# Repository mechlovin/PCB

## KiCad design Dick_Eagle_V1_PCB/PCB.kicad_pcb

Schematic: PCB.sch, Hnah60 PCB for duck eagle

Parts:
C1: 106; CP_Tantalum_3216
C2, C3: 105; C_0805_2012Metric
C4, C5, C6, C7: 104; C_0805_2012Metric
D1, D2, D3, D4, D5, D6, D7, D8, D9, D10, D11, D12, D13, D14, D15, D16, D17, D18, D19, D20, D21, D22, D23, D24, D25, D26, D27, D28, D29, D30, D31, D32, D33, D34, D35, D36, D37, D38, D39, D40, D41, D42, D43, D44, D45, D46, D47, D48, D49, D50, D51, D52, D53, D54, D56, D57, D58, D59, D60, D62, D63, D64, D65, D66: 4148; D_0805_Mab_ideal
D61, D67, D68, D69, D70, D71, D72, D73, D74, D75, D76, D77, D78, D79, D80, D81, D82, D83, D84, D85, D86, D87, D88, D89, D90, D92, D93, D94, D95, D97, D98, D99, D100, D101, D102, D103, D104, D105, D107, D108, D109, D110, D111, D112, D113, D114, D115, D116, D117, D118, D119, D120, D121, D122, D123, D124, D125, D126, D127, D128, D129, D130, D131, D132, D133, D134, D135, D136, D137, D138, D139, D153, D154, D155, D156, D157, D158: SMD; CHERRY_MX_LED_3MM
D91, D96, D106, D140: SK6812MINI; LED_SK6812MINI_PLCC4_3.5x3.5mm_P1.75mm
H1, H18, H22: Screw; Screw_M2_Hole
H2, H4, H6, H8, H11, H13, H14, H15, H16, H17, H19, H24: Stablilizer; Cherry_Stab_PCBMounted
H3, H5, H7, H9, H10, H12, H20, H21, H23: Screw; Screw_M2_hole_long_oval
J1: AVR-ISP-6; AVR_ISP_6
J2: Conn_01x06_Female; PinHeader_1x06_P1.27mm_Vertical
J3: USB_B_Mini; USB_MINIB
Q1: FDS9926A; SOIC-8_3.9x4.9mm_P1.27mm
R1, R2: 5k1; R_0805_2012Metric
R3, R6: 10k; R_0805_2012Metric
R4, R5: 22R; R_0805_2012Metric
R7, R8, R9, R10, R11, R12, R13, R14, R15, R16, R17, R18, R19, R20, R21, R22, R23, R24, R25, R27, R28, R29, R30, R32, R33, R34, R35, R37, R38, R39, R40, R41, R42, R43, R44, R45, R47, R48, R49, R50, R52, R53, R54, R55, R56, R57, R58, R59, R60, R61, R62, R63, R64, R65, R66, R67, R68, R69, R70, R71, R72, R73, R74, R75, R76: 330; R_0805_2012Metric
R26: 3300; R_0805_2012Metric
SW1: ESC; CHERRY_PCB_100H
SW2: TAB; CHERRY_PCB_100H
SW3, SW4: CAPS; CHERRY_PCB_100H
SW5, SW69, SW75: SHIFT; CHERRY_PCB_100H
SW6, SW7: CONTROL; CHERRY_PCB_100H
SW8: 1; CHERRY_PCB_100H
SW9: Q; CHERRY_PCB_100H
SW10: A; CHERRY_PCB_100H
SW11: Z; CHERRY_PCB_100H
SW12, SW44, SW49, SW61: GUI; CHERRY_PCB_100H
SW13: 2; CHERRY_PCB_100H
SW14: W; CHERRY_PCB_100H
SW15: S; CHERRY_PCB_100H
SW16: X; CHERRY_PCB_100H
SW17, SW43, SW50: ALTERNATE; CHERRY_PCB_100H
SW18: 3; CHERRY_PCB_100H
SW19: E; CHERRY_PCB_100H
SW20: D; CHERRY_PCB_100H
SW21: C; CHERRY_PCB_100H
SW22: 4; CHERRY_PCB_100H
SW23: R; CHERRY_PCB_100H
SW24: F; CHERRY_PCB_100H
SW25: V; CHERRY_PCB_100H
SW26: 5; CHERRY_PCB_100H
SW27: T; CHERRY_PCB_100H
SW28: G; CHERRY_PCB_100H
SW29: B; CHERRY_PCB_100H
SW30: 6; CHERRY_PCB_100H
SW31: Y; CHERRY_PCB_100H
SW32: H; CHERRY_PCB_100H
SW33: N; CHERRY_PCB_100H
SW34, SW59: SPACE; CHERRY_PCB_100H
SW35: 7; CHERRY_PCB_100H
SW36: U; CHERRY_PCB_100H
SW37: J; CHERRY_PCB_100H
SW38: M; CHERRY_PCB_100H
SW39: 8; CHERRY_PCB_100H
SW40: I; CHERRY_PCB_100H
SW41: K; CHERRY_PCB_100H
SW42: COMMA; CHERRY_PCB_100H
SW45: 9; CHERRY_PCB_100H
SW46: O; CHERRY_PCB_100H
SW47: L; CHERRY_PCB_100H
SW48: DOT; CHERRY_PCB_100H
SW51: 0; CHERRY_PCB_100H
SW52: P; CHERRY_PCB_100H
SW53: SCOLON; CHERRY_PCB_100H
SW54: SLASH; CHERRY_PCB_100H
SW55, SW66: APP; CHERRY_PCB_100H
SW56: MINUS; CHERRY_PCB_100H
SW57: LBRC; CHERRY_PCB_100H
SW58: QUOTE; CHERRY_PCB_100H
SW62, SW68: CTRL; CHERRY_PCB_100H
SW63: EQUAL; CHERRY_PCB_100H
SW64: RBRC; CHERRY_PCB_100H
SW65: HASH; CHERRY_PCB_100H
SW67: UP; CHERRY_PCB_100H
SW70, SW71: BSPC; CHERRY_PCB_100H
SW72: BSLS; CHERRY_PCB_100H
SW73, SW74: ENTER; CHERRY_PCB_100H
SW76: AFTER BSPC; CHERRY_PCB_100H
SW77: Reset; SW_SPST_FSMSM
U1: ATMEGA32U4; TQFP-44_Pitch0.8mm
USB1: HRO-TYPE-C-31-M-12; USB_MINI_MAB
Y1: 16MHz; Resonator_SMD_muRata_CSTxExxV-3Pin_3.0x1.1mm

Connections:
/Backlight-layout1: Q1.2 (G1), Q1.4 (G2), U1.12 ((PCINT7/OC0A/OC1C/~RTS~)PB7)
/Col1-layout1: J1.4 (MOSI), SW1.2, SW2.2, SW3.2, SW4.1, SW5.2, SW6.2, SW7.2, U1.10 ((PDI/PCINT2/MOSI)PB2)
/Col2-layout1: J1.3 (SCK), SW8.2, SW9.2, SW10.2, SW11.2, SW12.2, SW44.2, U1.9 ((PCINT1/SCLK)PB1)
/Col3-layout1: J1.1 (MISO), SW13.2, SW14.2, SW15.2, SW16.2, SW17.2, SW50.2, U1.11 ((PDO/PCINT3/MISO)PB3)
/Col4-layout1: SW18.2, SW19.2, SW20.2, SW21.2, U1.36 ((ADC7/TDI)PF7)
/Col5-layout1: SW22.2, SW23.2, SW24.2, SW25.2, U1.37 ((ADC6/TDO)PF6)
/Col6-layout1: SW26.2, SW27.2, SW28.2, SW29.2, U1.38 ((ADC5/TMS)PF5)
/Col7-layout1: SW30.2, SW31.2, SW32.2, SW33.2, SW34.2, SW59.2, U1.41 ((ADC0)PF0)
/Col8-layout1: SW35.2, SW36.2, SW37.2, SW38.2, U1.39 ((ADC4/TCK)PF4)
/Col9-layout1: SW39.2, SW40.2, SW41.2, SW42.2, U1.40 ((ADC1)PF1)
/Col10-layout1: SW43.2, SW45.2, SW46.2, SW47.2, SW48.2, U1.22 ((XCK1/~CTS~)PD5)
/Col11-layout1: SW49.2, SW51.2, SW52.2, SW53.2, SW54.2, SW61.2, U1.25 ((ICP1/ADC8)PD4)
/Col12-layout1: SW55.2, SW56.2, SW57.2, SW58.2, SW66.2, U1.26 ((T1/~OC4D~/ADC9)PD6)
/Col13-layout1: SW62.2, SW63.2, SW64.2, SW65.2, SW68.2, SW69.2, SW75.2, U1.27 ((T0/OC4D/ADC10)PD7)
/Col14-layout1: SW67.2, SW70.2, SW71.2, SW72.2, SW73.1, SW74.2, SW76.2, U1.28 ((PCINT4/ADC11)PB4)
/RGB-layout1: R6.2, R26.1, U1.33 ((~HWB~)PE2)
/Reset: J1.5 (~RST), R3.1, SW77.2, U1.13 (~RESET~)
/caps_led: D69.2 (A), D137.1 (K), U1.8 ((SS/PCINT0)PB0)
/row1-layout1: D1.1 (K), D6.1 (K), D11.1 (K), D16.1 (K), D20.1 (K), D24.1 (K), D28.1 (K), D33.1 (K), D37.1 (K), D42.1 (K), D47.1 (K), D52.1 (K), D57.1 (K), D62.1 (K), U1.31 ((OC3A/~OC4A~)PC6)
/row2-layout1: D2.1 (K), D7.1 (K), D12.1 (K), D17.1 (K), D21.1 (K), D25.1 (K), D29.1 (K), D34.1 (K), D38.1 (K), D43.1 (K), D48.1 (K), D53.1 (K), D58.1 (K), D63.1 (K), U1.32 ((ICP3/CLK0/OC4A)PC7)
/row3-layout1: D3.1 (K), D8.1 (K), D13.1 (K), D18.1 (K), D22.1 (K), D26.1 (K), D30.1 (K), D35.1 (K), D39.1 (K), D44.1 (K), D49.1 (K), D54.1 (K), D59.1 (K), D64.1 (K), U1.1 ((INT6/AIN0)PE6)
/row4-layout1: D4.1 (K), D9.1 (K), D14.1 (K), D19.1 (K), D23.1 (K), D27.1 (K), D31.1 (K), D36.1 (K), D40.1 (K), D45.1 (K), D50.1 (K), D60.1 (K), D65.1 (K), U1.30 ((PCINT6/OC1B/OC4B/ADC13)PB6)
/row5-layout1: D5.1 (K), D10.1 (K), D15.1 (K), D32.1 (K), D41.1 (K), D46.1 (K), D51.1 (K), D56.1 (K), D66.1 (K), U1.29 ((PCINT5/OC1A/~OC4B~/ADC12)PB5)
GND: C1.2, C2.2, C3.2, C4.2, C5.2, C6.2, C7.2, D61.1 (K), D67.2 (A), D68.2 (A), D70.2 (A), D71.2 (A), D72.2 (A), D73.2 (A), D74.2 (A), D75.2 (A), D76.2 (A), D77.2 (A), D78.2 (A), D79.2 (A), D80.2 (A), D81.2 (A), D82.2 (A), D83.2 (A), D84.2 (A), D85.2 (A), D86.2 (A), D87.2 (A), D88.2 (A), D89.2 (A), D90.2 (A), D91.2 (VSS), D92.2 (A), D93.2 (A), D94.2 (A), D95.2 (A), D96.2 (VSS), D97.2 (A), D98.2 (A), D99.2 (A), D100.2 (A), D101.2 (A), D102.2 (A), D103.2 (A), D104.2 (A), D105.2 (A), D106.2 (VSS), D107.2 (A), D108.2 (A), D109.2 (A), D110.2 (A), D111.1 (K), D112.2 (A), D113.2 (A), D114.2 (A), D115.2 (A), D116.2 (A), D117.2 (A), D118.2 (A), D119.2 (A), D120.2 (A), D121.2 (A), D122.2 (A), D123.2 (A), D124.2 (A), D125.2 (A), D126.2 (A), D127.2 (A), D128.2 (A), D129.2 (A), D130.2 (A), D131.2 (A), D132.2 (A), D133.2 (A), D134.2 (A), D135.2 (A), D136.2 (A), D138.2 (A), D139.2 (A), D140.2 (VSS), D153.1 (K), D154.2 (A), D155.1 (K), D156.1 (K), D157.2 (A), D158.1 (K), J1.6 (GND), J2.6, J3.5 (GND), J3.6 (Shield), R1.1, R2.1, R6.1, SW77.1, U1.5 (UGnd), U1.15 (GND), U1.23 (GND), U1.35 (GND), U1.43 (GND), USB1.1 (GND), USB1.12 (GND), USB1.13 (SHIELD), Y1.2; also elsewhere on the board
unnamed: C3.1, U1.6 (Ucap)
unnamed: D1.2 (A), SW1.1
unnamed: D2.2 (A), SW2.1
unnamed: D3.2 (A), SW3.1, SW4.2
unnamed: D4.2 (A), SW5.1
unnamed: D5.2 (A), SW6.1, SW7.1
unnamed: D6.2 (A), SW8.1
unnamed: D7.2 (A), SW9.1
unnamed: D8.2 (A), SW10.1
unnamed: D9.2 (A), SW11.1
unnamed: D10.2 (A), SW12.1, SW44.1
unnamed: D11.2 (A), SW13.1
unnamed: D12.2 (A), SW14.1
unnamed: D13.2 (A), SW15.1
unnamed: D14.2 (A), SW16.1
unnamed: D15.2 (A), SW17.1, SW50.1
unnamed: D16.2 (A), SW18.1
unnamed: D17.2 (A), SW19.1
unnamed: D18.2 (A), SW20.1
unnamed: D19.2 (A), SW21.1
unnamed: D20.2 (A), SW22.1
unnamed: D21.2 (A), SW23.1
unnamed: D22.2 (A), SW24.1
unnamed: D23.2 (A), SW25.1
unnamed: D24.2 (A), SW26.1
unnamed: D25.2 (A), SW27.1
unnamed: D26.2 (A), SW28.1
unnamed: D27.2 (A), SW29.1
unnamed: D28.2 (A), SW30.1
unnamed: D29.2 (A), SW31.1
unnamed: D30.2 (A), SW32.1
unnamed: D31.2 (A), SW33.1
unnamed: D32.2 (A), SW34.1, SW59.1
unnamed: D33.2 (A), SW35.1
unnamed: D34.2 (A), SW36.1
unnamed: D35.2 (A), SW37.1
unnamed: D36.2 (A), SW38.1
unnamed: D37.2 (A), SW39.1
unnamed: D38.2 (A), SW40.1
unnamed: D39.2 (A), SW41.1
unnamed: D40.2 (A), SW42.1
unnamed: D41.2 (A), SW43.1
unnamed: D42.2 (A), SW45.1
unnamed: D43.2 (A), SW46.1
unnamed: D44.2 (A), SW47.1
unnamed: D45.2 (A), SW48.1
unnamed: D46.2 (A), SW49.1, SW61.1
unnamed: D47.2 (A), SW51.1
unnamed: D48.2 (A), SW52.1
unnamed: D49.2 (A), SW53.1
unnamed: D50.2 (A), SW54.1
unnamed: D51.2 (A), SW55.1, SW66.1
unnamed: D52.2 (A), SW56.1
unnamed: D53.2 (A), SW57.1
unnamed: D54.2 (A), SW58.1
unnamed: D56.2 (A), SW62.1, SW68.1
unnamed: D57.2 (A), SW63.1
unnamed: D58.2 (A), SW64.1
unnamed: D59.2 (A), SW65.1
unnamed: D60.2 (A), SW69.1, SW75.1
unnamed: D61.2 (A), D71.1 (K), R11.2
unnamed: D62.2 (A), SW70.1, SW71.1
unnamed: D63.2 (A), SW72.1
unnamed: D64.2 (A), SW73.2, SW74.1
unnamed: D65.2 (A), SW67.1
unnamed: D66.2 (A), SW76.1
unnamed: D67.1 (K), R7.2
unnamed: D68.1 (K), R8.2
unnamed: D72.1 (K), R12.2
unnamed 93: D73.1 (K), R13.2; also elsewhere on the board
unnamed: D74.1 (K), R14.2
unnamed: D75.1 (K), R15.2
unnamed: D77.1 (K), R17.2
unnamed: D78.1 (K), R18.2
unnamed: D79.1 (K), R19.2
unnamed: D80.1 (K), R20.2
unnamed: D82.1 (K), R22.2
unnamed: D83.1 (K), R23.2
unnamed: D84.1 (K), R24.2
unnamed: D85.1 (K), R25.2
unnamed: D87.1 (K), R27.2
unnamed: D88.1 (K), R28.2
unnamed: D89.1 (K), R29.2
unnamed: D90.1 (K), R30.2
unnamed: D91.1 (DOUT), D96.3 (DIN)
unnamed: D92.1 (K), R32.2
unnamed: D93.1 (K), R33.2
unnamed: D94.1 (K), R34.2
unnamed: D95.1 (K), R35.2
unnamed: D97.1 (K), R37.2
unnamed: D98.1 (K), R38.2
unnamed: D99.1 (K), R39.2
unnamed: D100.1 (K), R40.2
unnamed: D101.1 (K), D154.1 (K), R41.2
unnamed: D102.1 (K), R42.2
unnamed: D103.1 (K), R43.2
unnamed: D104.1 (K), R44.2
unnamed: D105.1 (K), R45.2
unnamed: D106.1 (DOUT), D140.3 (DIN)
unnamed: D91.3 (DIN), D106.3 (DIN), R26.2
unnamed: D107.1 (K), R47.2
unnamed: D108.1 (K), R48.2
unnamed: D109.1 (K), R49.2
unnamed: D110.1 (K), R50.2
unnamed: D76.1 (K), D111.2 (A), R16.2
unnamed: D112.1 (K), R52.2
unnamed: D113.1 (K), R53.2
unnamed: D114.1 (K), R54.2
unnamed: D115.1 (K), R55.2
unnamed: D116.1 (K), R56.2
unnamed: D117.1 (K), R57.2
unnamed: D118.1 (K), R58.2
unnamed: D119.1 (K), R59.2
unnamed: D120.1 (K), R60.2
unnamed: D121.1 (K), D155.2 (A), R61.2
unnamed: D122.1 (K), R62.2
unnamed: D123.1 (K), R63.2
unnamed: D124.1 (K), R64.2
unnamed: D125.1 (K), R65.2
unnamed: D126.1 (K), D156.2 (A), R66.2
unnamed: D127.1 (K), R67.2
unnamed: D128.1 (K), R68.2
unnamed: D129.1 (K), R69.2
unnamed: D130.1 (K), D157.1 (K), R70.2
unnamed: D131.1 (K), D158.2 (A), R71.2
unnamed: D86.1 (K), D132.1 (K), R72.2
unnamed: D133.1 (K), R73.2
unnamed: D134.1 (K), D138.1 (K), R74.2
unnamed: D135.1 (K), R75.2
unnamed: D136.1 (K), R76.2
unnamed: D69.1 (K), D137.2 (A), R9.2
unnamed: D70.1 (K), D139.1 (K), R10.2
unnamed: D81.1 (K), D153.2 (A), R21.2
unnamed: J2.2, U1.21 ((TXD1/INT3)PD3)
unnamed: J2.3, U1.20 ((RXD1/INT2)PD2)
unnamed: J2.4, U1.19 ((SDA/INT1)PD1)
unnamed: J2.5, U1.18 ((OC0B/SCL/INT0)PD0)
unnamed: J3.2 (D-), R4.2, USB1.5 (DN2), USB1.7 (DN1)
unnamed: J3.3 (D+), R5.2, USB1.6 (DP1), USB1.8 (DP2)
unnamed: Q1.1 (S1), Q1.3 (S2), R7.1, R8.1, R10.1, R11.1, R12.1, R13.1, R14.1, R15.1, R16.1, R17.1, R18.1, R19.1, R20.1, R21.1, R22.1, R23.1, R24.1, R25.1, R27.1, R28.1, R29.1, R30.1, R32.1, R33.1, R34.1, R35.1, R37.1, R38.1, R39.1, R40.1, R41.1, R42.1, R43.1, R44.1, R45.1, R47.1, R48.1, R49.1, R50.1, R52.1, R53.1, R54.1, R55.1, R56.1, R57.1, R58.1, R59.1, R60.1, R61.1, R62.1, R63.1, R64.1, R65.1, R66.1, R67.1, R68.1, R69.1, R70.1, R71.1, R72.1, R73.1, R74.1, R75.1, R76.1
unnamed: R1.2, USB1.10 (CC2)
unnamed: R2.2, USB1.4 (CC1)
unnamed: R4.1, U1.3 (D-)
unnamed: R5.1, U1.4 (D+)
unnamed: U1.16 (XTAL2), Y1.1
unnamed: U1.17 (XTAL1), Y1.3
VCC: C1.1, C2.1, C4.1, C5.1, C6.1, C7.1, D91.4 (VDD), D96.4 (VDD), D106.4 (VDD), D140.4 (VDD), J1.2 (VCC), J2.1, J3.1 (VBUS), Q1.5 (D2), Q1.6 (D2), Q1.7 (D1), Q1.8 (D1), R3.2, R9.1, U1.2 (UVcc), U1.7 (VBus), U1.14 (VCC), U1.24 (AVCC), U1.34 (VCC), U1.44 (AVCC), USB1.2 (VBUS), USB1.11 (VBUS)

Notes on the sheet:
M2 screw hole fixed
M2 screw oval hole
Cherry stabilizer pcb mounted
Backlight LED & Indicator LED
Key Matrix
RGB LED side
Note:
Controller Atmega32u4 Connector ISP programmer

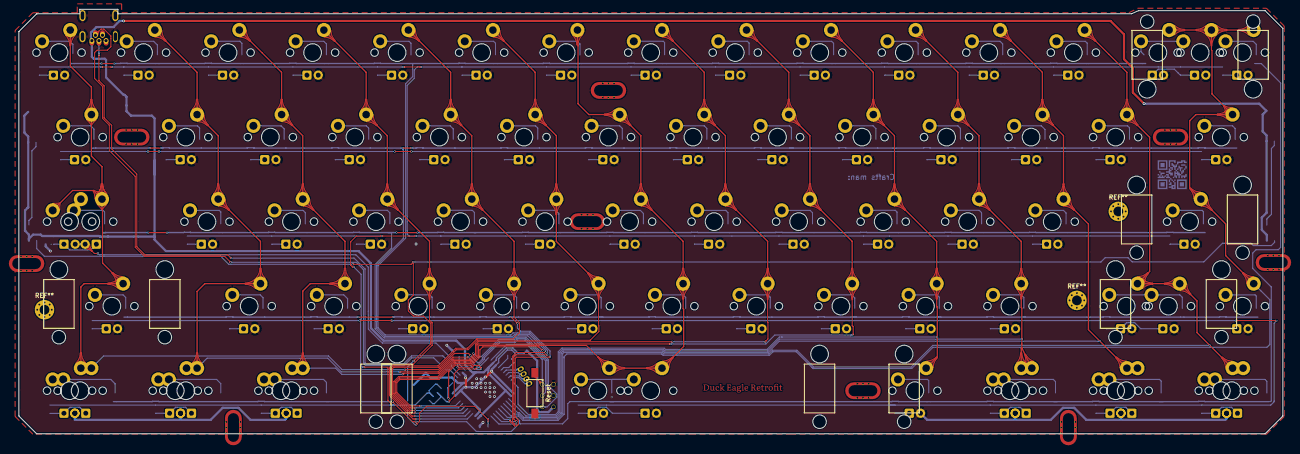
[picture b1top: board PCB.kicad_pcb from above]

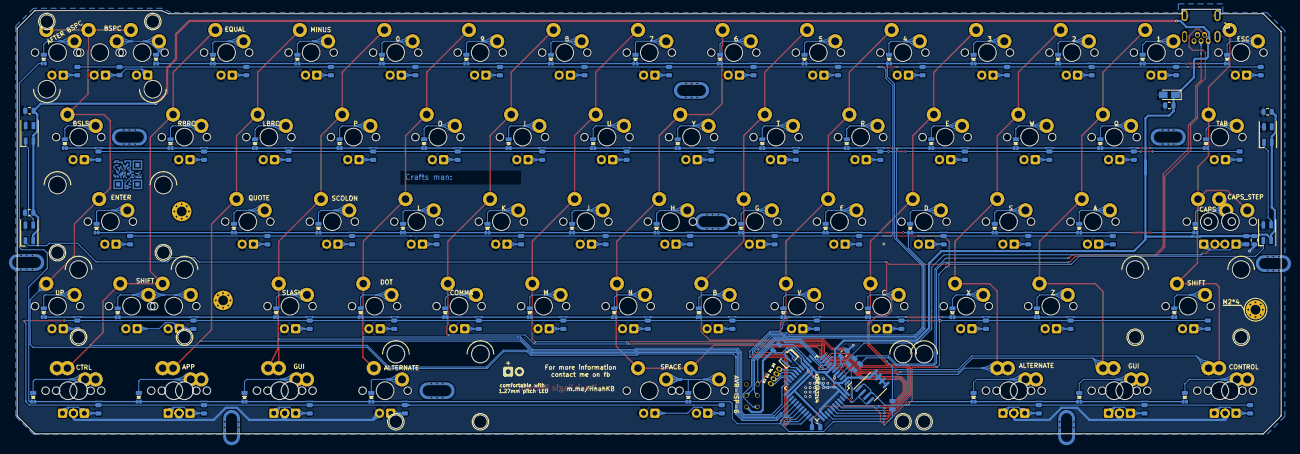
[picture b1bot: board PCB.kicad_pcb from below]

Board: 2 copper layers, 284.9 x 95.7 mm, 316 parts (148 on the bottom side), 162 nets.

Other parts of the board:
D73#2: SMD; CHERRY_MX_LED_3MM

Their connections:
GND: D73#2.2; also elsewhere on the board
unnamed 93: D73#2.1; also elsewhere on the board

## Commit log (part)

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2019-11-02 Create Hannah910.step
    update .step file for Hannah910 PCB
2019-11-04 add new duck eagle pcb
    replace pcb for duck eagle v1
2019-11-10 add new TKL keyboard
2019-12-05 update json file
2020-04-23 xóa file không nên chia sẻ
2020-05-08 add Adelais .step file
2020-05-09 add via firmware
2020-05-30 update
    InfinityCE: update NKRO function
2020-06-02 update firmware
2020-06-03 change name
2020-06-06 add infinity87
2020-07-07 Create Hannah60-DuckEagle.step
    Duck Eagle V1 compatible
2020-07-22 update delphine PCB
2020-07-23 add infinity88, delphine firmware
    Infinity88 3D model
    Delphine Firmware for RGB version and mono LED version
2020-09-15 update adelais firmware
2020-09-22 Create Hannah65-Rev1.step
    Ađ hannah65 rev.1 PCB
2020-09-25 add Hannah60PCB-Rev.2 .step file
2020-11-18 add firmware
2021-01-05 add infinity88 and kyuu plate
2021-01-12 Add Common60PCB
    Add gerber file, BOM
2021-01-24 add vial firmware
2021-02-22 add 1800 compact keyboard
2021-05-19 add adelais, haus, hex6C firmware
2021-06-12 update adelais standard firmware
2021-06-14 add kanu firmwaer
2021-07-09 update daughter board
2021-07-16 add IF85.7 PCB
2021-08-04 update firmware, bootloader
2021-08-04 update sessantacinque firmware
2021-08-05 add db
2021-08-07 add USBasploader-atmega32a
2021-08-20 add Hex4B Firmware
2021-10-30 update 30102021
2021-11-08 update 08112021
    Update Jay60 firmware, Adelais APM32F103, IF87.5 .step file
2021-11-11 add olly BB firmware
2021-11-12 Update mechlovin_infinity87_rev1_rouge87_via.bin
    Update Caps LED state
2021-11-25 update IF87.5C .step file
2021-11-27 add Rouge87 Plate .dwg file
2021-12-23 Change folder name
2021-12-24 update 24122021
2021-12-27 add TMKL keyboard
2021-12-31 update 31122021
2022-01-09 add spark67
2022-01-24 add infinity87_rev2
2022-02-15 add LZ-Erghost
2022-03-07 add IF87 RGB
2022-05-04 Add Kay65
2022-05-10 add Neon
2022-06-16 update 16062022
2022-07-22 add E6V2 and UTD356mini plate file
2022-08-14 add Kay converter
2022-08-14 add gerber file
2022-09-11 add OTD35mini converter
2022-09-24 add Kay converter Rev2
2022-09-24 move Kay converter to Converter folder
2022-10-28 update kay65 firmware
2022-12-02 update kay60, adelais
2022-12-10 add Zed65 Mono-LED
2022-12-19 add Zed65-MonoLED
2022-12-22 Update ANC Rev3 Firmware
    Fix green underglow LED
2022-12-22 update PID
2022-12-22 Add encoder on ANC VIA V3
2023-03-16 add Olly orion, octagon
2023-05-15 update 15052023
    add zed60, zed65 rv1, if875 rev2
2023-05-26 add Black Bird & JetFire plate files
2023-06-16 add Zed65 Rev. 1 step PCB files
2023-07-07 add IF87.5 Rev.2 PCB
2023-09-07 add olly JF rev2, Alveus
2023-10-25 add zed65-rgb
2024-02-29 Update mechlovin_kay60_via.hex
    Fixed Kay60 don't weak after sleep for Mac M1
2024-05-15 update if87 rev3 firmware
2024-05-15 update if87/rev3/rouge
2024-05-16 update if87/rev3 firmware
2024-05-27 update Olly-TCV3 firmware
2024-05-31 add Rev3 HS firmware
    Firmware chỉ dành cho phiên bản bán qua web Mechlovin.
2024-07-29 add lz ghost cp
2024-08-12 update rouge87 rev3 - nika art
    fix indicator LED state
2025-01-06 Create MKP-ZED60-R1.2-C-JST_SH_SUR-06012025.step
    Add Zed60 Rev1.2 Step file
2025-01-13 add ollybb rev2 firmware
2025-01-21 reallocate GAF910 and GSK910 Firmware
2025-01-21 correct folder name
2025-02-18 update mechlovin9 rev3 firmware
2025-02-24 update olly octagon firmware
    enable control backlight on VIA
2025-03-05 update zed65 firmware
    Allow control RGB light in VIA lighting menu
2025-03-06 update rouge87 firmware and json
    the OTD360 compatible PCB
2025-03-06 add firmware for NRD Kaze
2025-03-06 rename nrd kaze firmware
2025-03-11 Update mechlovin_infinity87_rev2_via.hex
    correct state LED indicator
2025-03-12 update otd tkl compatible plate
2025-03-17 remove picture
2025-04-04 add rev3 firmware and json for nrd kaze PCB
2025-04-04 add support for pz65 firmware and zed65 hotswapPCB
2025-04-06 update zed60 and if875
2025-04-16 update zed65 rev1.2 solder firmware
2025-05-06 add jjw cloudline2
2025-05-15 update zed65 Rev1.2 firmware
2025-05-16 update rgblight mode
    cập nhật tắt cứng tất cả LED khi chọn all-off trong VIA menu
2025-05-16 renname
2025-05-16 update toggle LED state
2025-08-21 add zed75-ak01 firmware and update IF87HS, CL2 Firmware
2025-09-17 Update mechlovin_infinity87_rev3_standard_via.bin
    Allow test matrix in VIA
2025-12-09 Add support for Zed75-Tomo
2025-12-17 add solder firmware
2026-01-12 add MKP-DB-C3-SH-Rev3
2026-01-20 update zed65-kohaku firmware
2026-03-18 add Adelais Rev5, Zed65 RGB Rev1
2026-05-11 update zed65-910 json, cor65 json and if87.5 json
2026-05-26 Update zed65-910-rev2.json
    update lighting keycode
2026-05-26 Add keycodes for QMK lighting support
2026-05-28 update step file for IF87HS and IF88HS
